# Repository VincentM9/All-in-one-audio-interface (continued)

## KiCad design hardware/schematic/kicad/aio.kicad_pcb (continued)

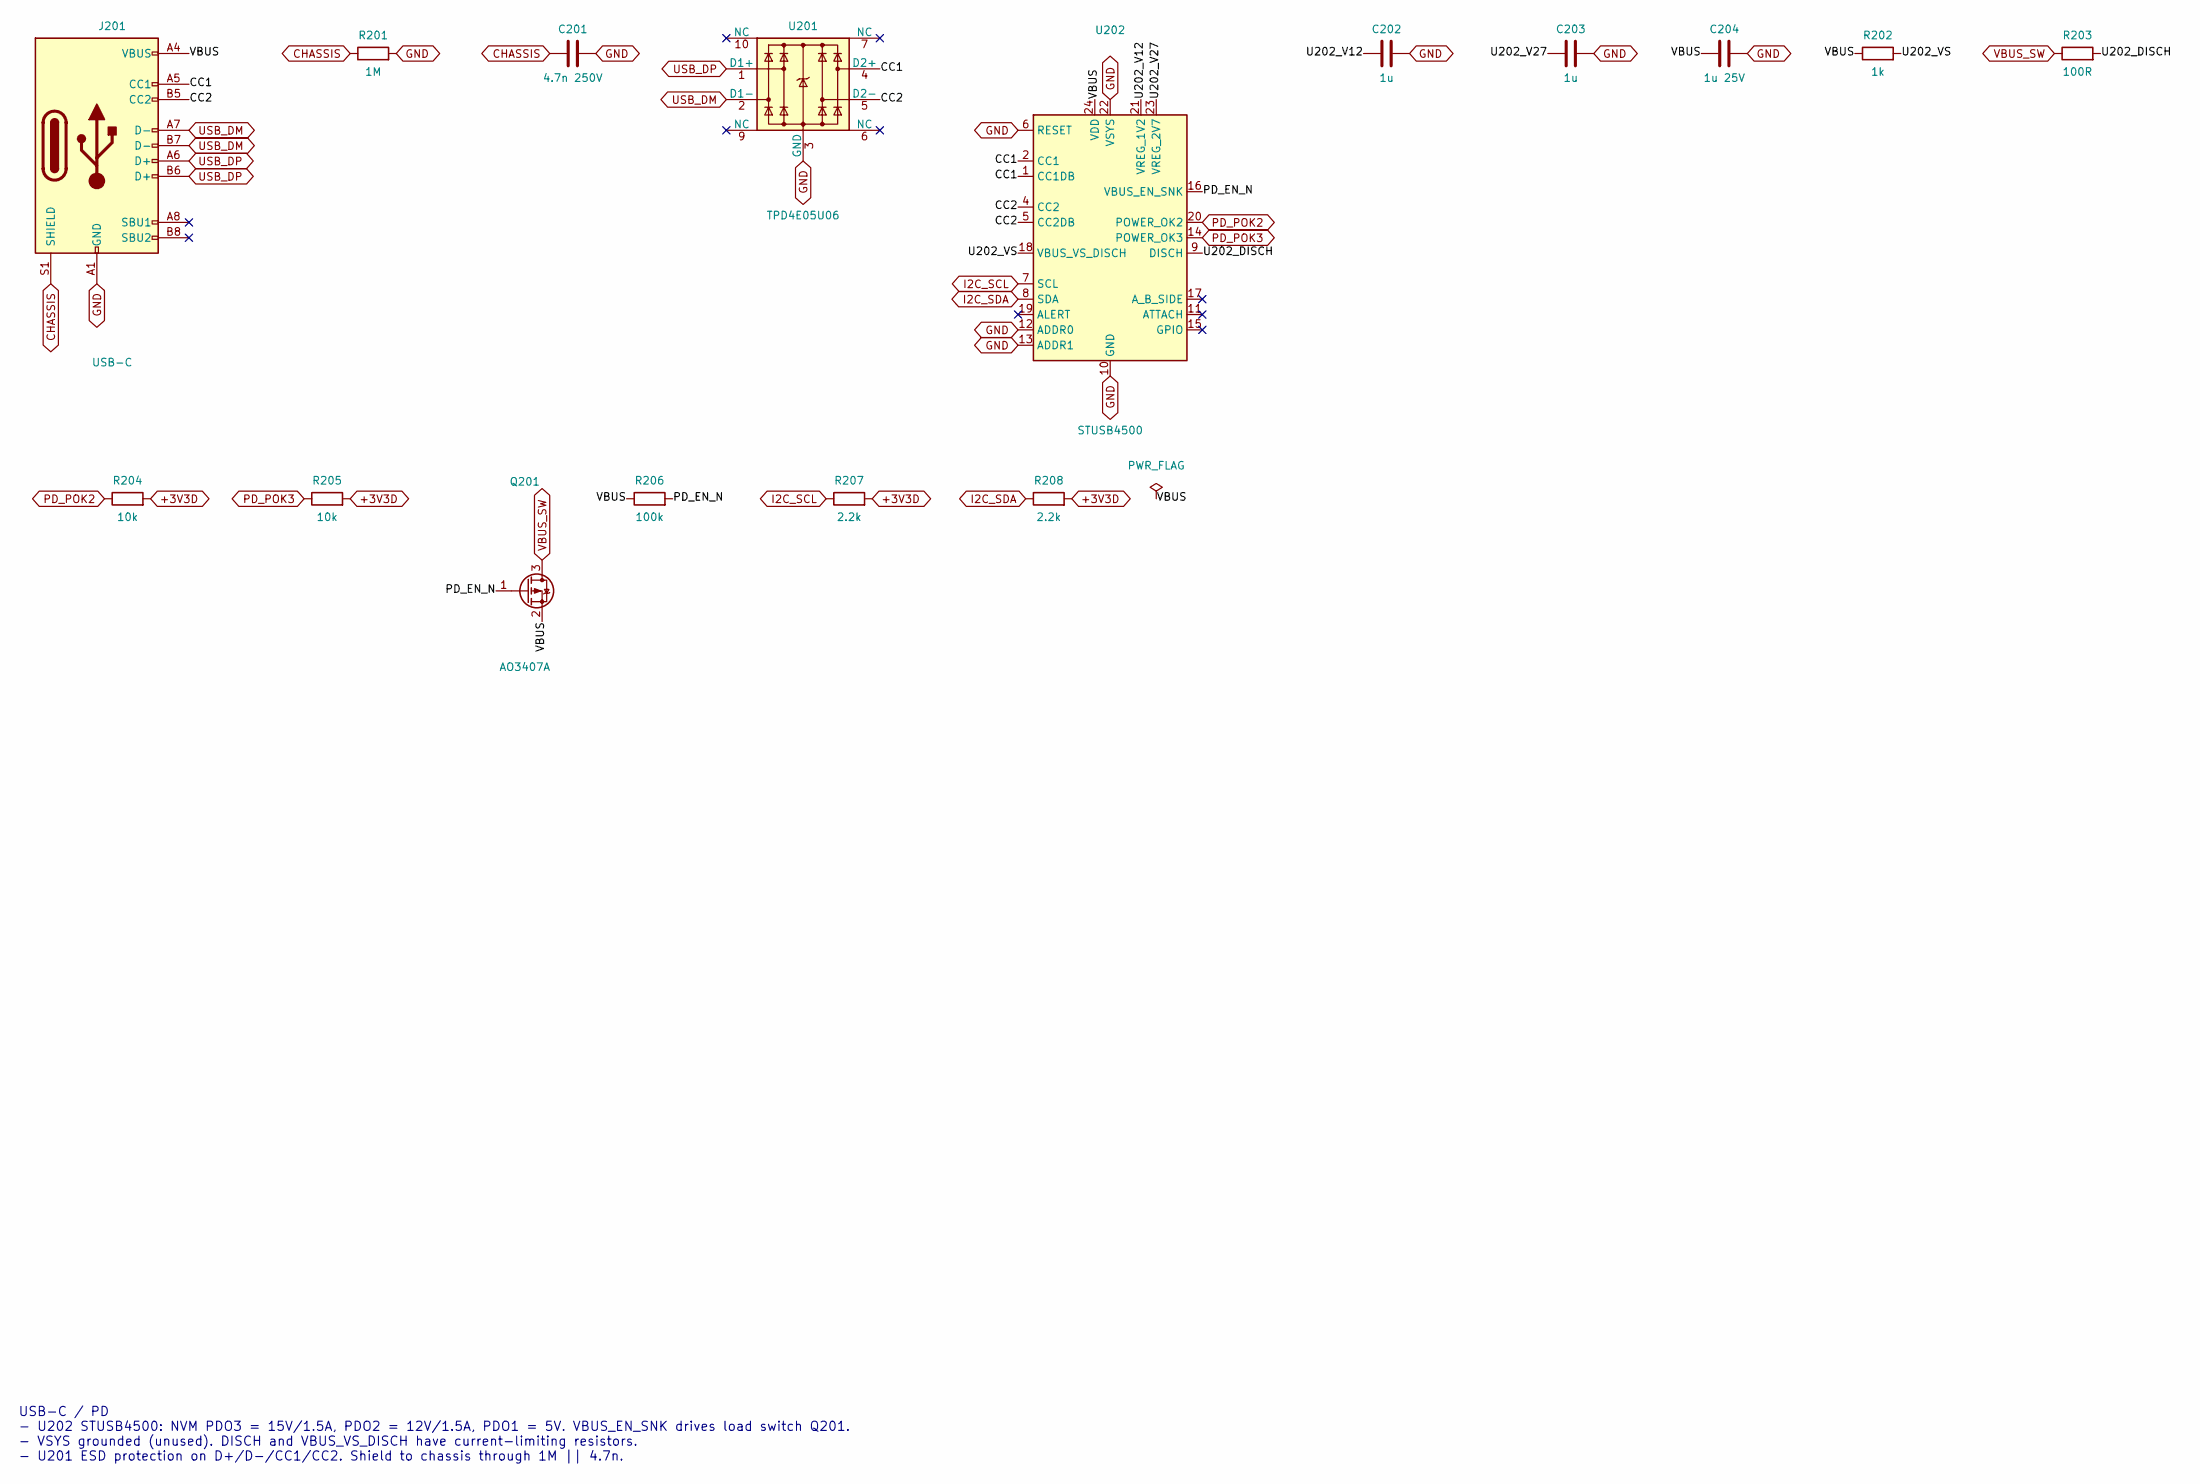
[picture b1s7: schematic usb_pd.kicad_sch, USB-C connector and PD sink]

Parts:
C201: 4.7n 250V; C_1206_3216Metric
C202, C203: 1u; C_0603_1608Metric
C204: 1u 25V; C_0805_2012Metric
J201: USB-C; USB_C_Receptacle_GCT_USB4105-xx-A_16P_TopMnt_Horizontal; MPN USB4105-GF-A
Q201: AO3407A; SOT-23; MPN AO3407A
R201: 1M; R_0603_1608Metric
R202: 1k; R_0603_1608Metric
R203: 100R; R_0805_2012Metric
R204, R205: 10k; R_0603_1608Metric
R206: 100k; R_0603_1608Metric
R207, R208: 2.2k; R_0603_1608Metric
U201: TPD4E05U06; USON-10_2.5x1.0mm_P0.5mm; MPN TPD4E05U06DQAR
U202: STUSB4500; QFN-24-1EP_4x4mm_P0.5mm_EP2.7x2.7mm; MPN STUSB4500QTR

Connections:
+3V3D: R204.2, R205.2, R207.2, R208.2; also elsewhere on the board
CC1: J201.A5 (CC1), U201.4 (D2+), U202.1 (CC1DB), U202.2 (CC1)
CC2: J201.B5 (CC2), U201.5 (D2-), U202.4 (CC2), U202.5 (CC2DB)
CHASSIS: C201.1, J201.S1 (SHIELD), R201.1; also elsewhere on the board
GND: C201.2, C202.2, C203.2, C204.2, J201.A1 (GND), J201.A12 (GND), J201.B1 (GND), J201.B12 (GND), R201.2, U201.3 (GND), U201.8 (GND), U202.6 (RESET), U202.10 (GND), U202.12 (ADDR0), U202.13 (ADDR1), U202.22 (VSYS), U202.25 (GND); also elsewhere on the board
I2C_SCL: R207.1, U202.7 (SCL)
I2C_SDA: R208.1, U202.8 (SDA)
PD_EN_N: Q201.1 (G), R206.2, U202.16 (VBUS_EN_SNK)
PD_POK2: R204.1, U202.20 (POWER_OK2)
PD_POK3: R205.1, U202.14 (POWER_OK3)
U202_DISCH: R203.2, U202.9 (DISCH)
U202_V12: C202.1, U202.21 (VREG_1V2)
U202_V27: C203.1, U202.23 (VREG_2V7)
U202_VS: R202.2, U202.18 (VBUS_VS_DISCH)
USB_DM: J201.A7 (D-), J201.B7 (D-), U201.2 (D1-)
USB_DP: J201.A6 (D+), J201.B6 (D+), U201.1 (D1+)
VBUS: C204.1, J201.A4 (VBUS), J201.A9 (VBUS), J201.B4 (VBUS), J201.B9 (VBUS), Q201.2 (S), R202.1, R206.1, U202.24 (VDD)
VBUS_SW: Q201.3 (D), R203.1; also elsewhere on the board

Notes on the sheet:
USB-C / PD - U202 STUSB4500: NVM PDO3 = 15V/1.5A, PDO2 = 12V/1.5A, PDO1 = 5V. VBUS_EN_SNK drives load switch Q201. - VSYS grounded (unused). DISCH and VBUS_VS_DISCH have current-limiting resistors. - U201 ESD protection on D+/D-/CC1/CC2. Shield to chassis through 1M || 4.7n.

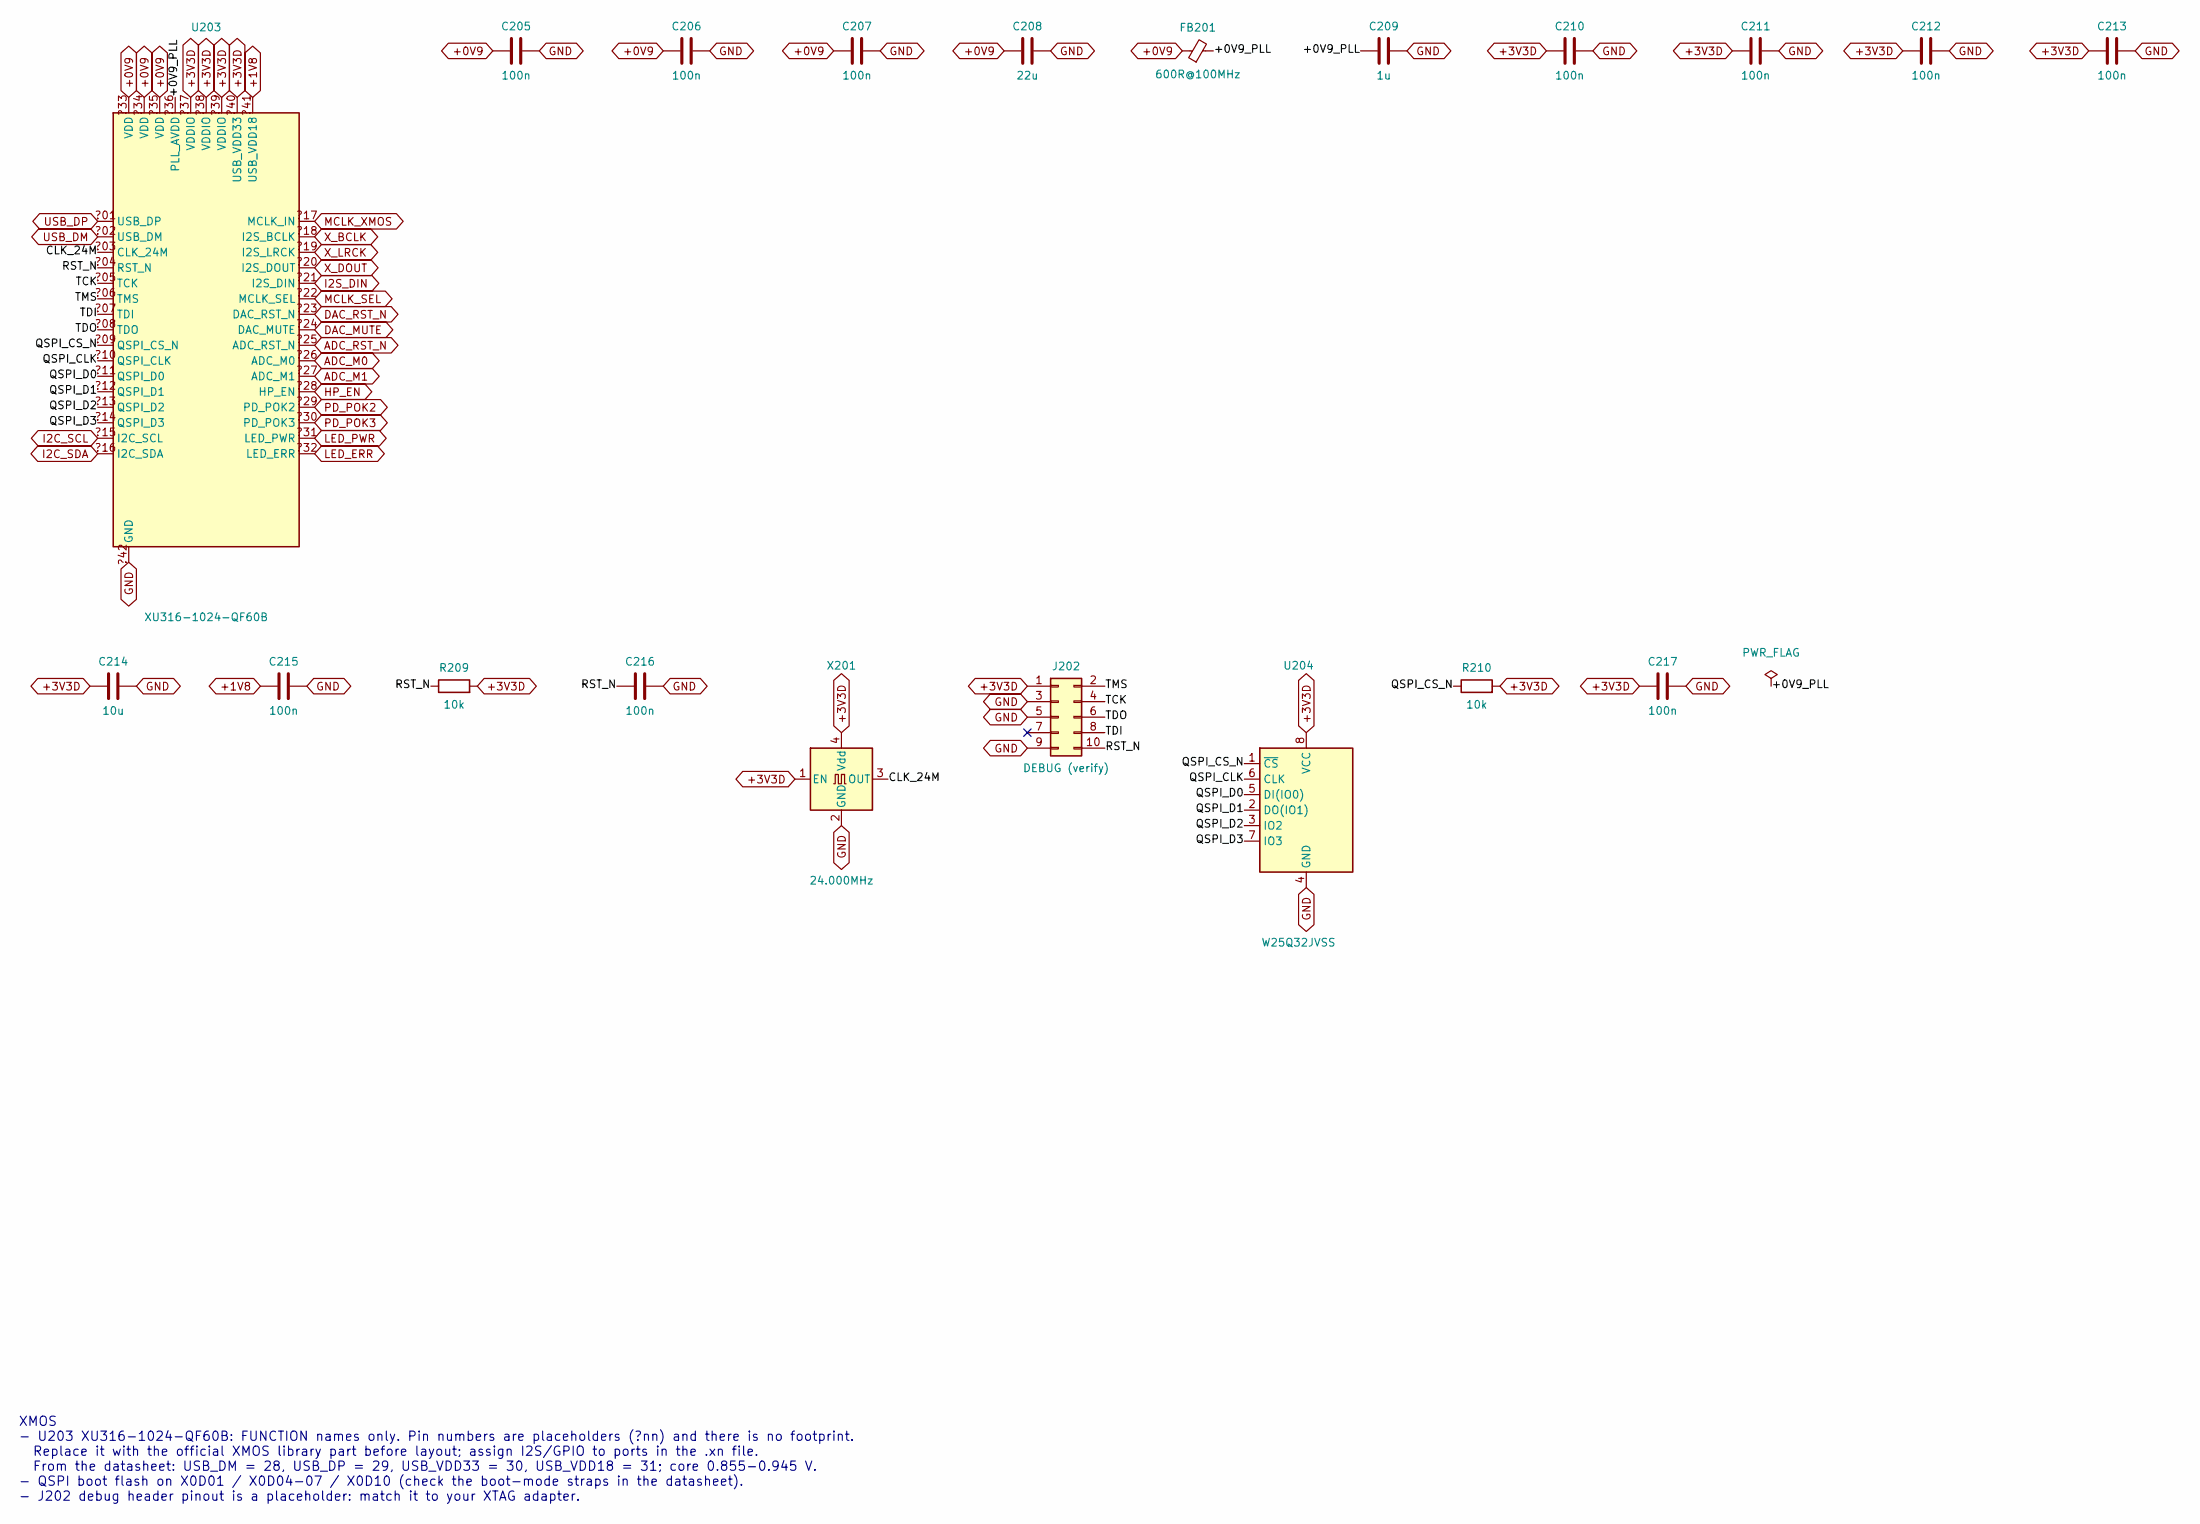
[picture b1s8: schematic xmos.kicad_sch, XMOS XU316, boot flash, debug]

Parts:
C205, C206, C207, C210, C211, C212, C213, C215, C216, C217: 100n; C_0603_1608Metric
C208: 22u; C_0805_2012Metric
C209: 1u; C_0603_1608Metric
C214: 10u; C_0805_2012Metric
FB201: 600R@100MHz; L_0805_2012Metric
J202: DEBUG (verify); PinHeader_2x05_P1.27mm_Vertical
R209, R210: 10k; R_0603_1608Metric
U203: XU316-1024-QF60B; MPN XU316-1024-QF60B-C24
U204: W25Q32JVSS; SOIC-8_5.23x5.23mm_P1.27mm; MPN W25Q32JVSSIQ
X201: 24.000MHz; Oscillator_SMD_Abracon_ASE-4Pin_3.2x2.5mm; MPN ASE-24.000MHZ-LC-T

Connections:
+0V9: C205.1, C206.1, C207.1, C208.1, FB201.1, U203.?33 (VDD), U203.?34 (VDD), U203.?35 (VDD); also elsewhere on the board
+0V9_PLL: C209.1, FB201.2, U203.?36 (PLL_AVDD)
+1V8: C215.1, U203.?41 (USB_VDD18); also elsewhere on the board
+3V3D: C210.1, C211.1, C212.1, C213.1, C214.1, C217.1, J202.1, R209.2, R210.2, U203.?37 (VDDIO), U203.?38 (VDDIO), U203.?39 (VDDIO), U203.?40 (USB_VDD33), U204.8 (VCC), X201.1 (EN), X201.4 (Vdd); also elsewhere on the board
CLK_24M: U203.?03 (CLK_24M), X201.3 (OUT)
GND: C205.2, C206.2, C207.2, C208.2, C209.2, C210.2, C211.2, C212.2, C213.2, C214.2, C215.2, C216.2, C217.2, J202.3, J202.5, J202.9, U203.?42 (GND), U204.4 (GND), X201.2 (GND); also elsewhere on the board
QSPI_CLK: U203.?10 (QSPI_CLK), U204.6 (CLK)
QSPI_CS_N: R210.1, U203.?09 (QSPI_CS_N), U204.1 (~CS)
QSPI_D0: U203.?11 (QSPI_D0), U204.5 (DI(IO0))
QSPI_D1: U203.?12 (QSPI_D1), U204.2 (DO(IO1))
QSPI_D2: U203.?13 (QSPI_D2), U204.3 (IO2)
QSPI_D3: U203.?14 (QSPI_D3), U204.7 (IO3)
RST_N: C216.1, J202.10, R209.1, U203.?04 (RST_N)
TCK: J202.4, U203.?05 (TCK)
TDI: J202.8, U203.?07 (TDI)
TDO: J202.6, U203.?08 (TDO)
TMS: J202.2, U203.?06 (TMS)

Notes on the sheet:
XMOS - U203 XU316-1024-QF60B: FUNCTION names only. Pin numbers are placeholders (?nn) and there is no footprint. Replace it with the official XMOS library part before layout; assign I2S/GPIO to ports in the .xn file. From the datasheet: USB_DM = 28, USB_DP = 29, USB_VDD33 = 30, USB_VDD18 = 31; core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

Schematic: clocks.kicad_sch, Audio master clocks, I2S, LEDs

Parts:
C218, C219, C220: 100n; C_0603_1608Metric
D201: green; LED_0805_2012Metric
D202: red; LED_0805_2012Metric
R211, R212, R213: 22R; R_0603_1608Metric
R214, R215, R216: 33R; R_0603_1608Metric
R217, R218: 330R; R_0603_1608Metric
U205: 74LVC1G3157; SOT-363_SC-70-6; MPN SN74LVC1G3157DCKR
X202: 24.576MHz; Oscillator_SMD_Abracon_ASE-4Pin_3.2x2.5mm; MPN NZ2520SDA-24.576M (low phase noise)
X203: 22.5792MHz; Oscillator_SMD_Abracon_ASE-4Pin_3.2x2.5mm; MPN NZ2520SDA-22.5792M (low phase noise)

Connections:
+3V3A: C218.1, C219.1, C220.1, U205.5 (VCC), X202.1 (EN), X202.4 (Vdd), X203.1 (EN), X203.4 (Vdd); also elsewhere on the board
GND: C218.2, C219.2, C220.2, D201.1 (K), D202.1 (K), U205.2 (GND), X202.2 (GND), X203.2 (GND); also elsewhere on the board
I2S_BCLK: R214.2; also elsewhere on the board
I2S_DOUT: R216.2; also elsewhere on the board
I2S_LRCK: R215.2; also elsewhere on the board
LED_ERR: R218.1
LED_ERR_A: D202.2 (A), R218.2
LED_PWR: R217.1
LED_PWR_A: D201.2 (A), R217.2
MCLK_44: U205.1, X203.3 (OUT)
MCLK_48: U205.3, X202.3 (OUT)
MCLK_ADC: R213.2; also elsewhere on the board
MCLK_DAC: R212.2; also elsewhere on the board
MCLK_MUX: R211.1, R212.1, R213.1, U205.4
MCLK_SEL: U205.6
MCLK_XMOS: R211.2
X_BCLK: R214.1
X_DOUT: R216.1
X_LRCK: R215.1

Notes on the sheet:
CLOCKS / I2S - X202 24.576 MHz (48 kHz family) and X203 22.5792 MHz (44.1 kHz family), selected by U205 (MCLK_SEL = 0 -> 48k). - Mux output fans out through 22R to XMOS, DAC and ADC. XMOS drives BCLK / LRCK / DOUT through 33R.

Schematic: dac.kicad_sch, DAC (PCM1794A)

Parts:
C301, C303, C305, C307, C309, C310: 10u; C_0805_2012Metric
C302, C304, C306, C308: 100n; C_0603_1608Metric
R301: 16k; R_0603_1608Metric
R302, R303, R304, R306: 10k; R_0603_1608Metric
R305, R307: 10k; R_0603_1608Metric; not fitted
U301: PCM1794A; SSOP-28_5.3x10.2mm_P0.65mm; MPN PCM1794ADBR

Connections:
+3V3A: C307.1, C308.1, R303.2, R305.2, R307.2, U301.9 (VDD); also elsewhere on the board
+5VA: C301.1, C302.1, C303.1, C304.1, C305.1, C306.1, U301.15 (VCC2R), U301.23 (VCC1), U301.28 (VCC2L); also elsewhere on the board
DAC_FMT0: R304.1, R305.1, U301.11 (FMT0)
DAC_FMT1: R306.1, R307.1, U301.12 (FMT1)
DAC_MUTE: R303.1, U301.10 (MUTE)
DAC_RST_N: R302.1, U301.14 (~RST)
GND: C301.2, C302.2, C303.2, C304.2, C305.2, C306.2, C307.2, C308.2, C309.2, C310.2, R301.2, R302.2, R304.2, R306.2, U301.1 (MONO), U301.2 (CHSL), U301.3 (DEM), U301.8 (DGND), U301.16 (AGND3R), U301.19 (AGND1), U301.24 (AGND2), U301.27 (AGND3L); also elsewhere on the board
I2S_BCLK: U301.6 (BCK); also elsewhere on the board
I2S_DOUT: U301.5 (DATA); also elsewhere on the board
I2S_LRCK: U301.4 (LRCK); also elsewhere on the board
IL_N: U301.26 (IOUTL-); also elsewhere on the board
IL_P: U301.25 (IOUTL+); also elsewhere on the board
IREF: R301.1, U301.20 (IREF)
IR_N: U301.18 (IOUTR-); also elsewhere on the board
IR_P: U301.17 (IOUTR+); also elsewhere on the board
MCLK_DAC: U301.7 (SCK); also elsewhere on the board
VCOML: C309.1, U301.22 (VCOML)
VCOMR: C310.1, U301.21 (VCOMR)

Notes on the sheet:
DAC NOTES - U301 PCM1794A (hardware control). Output 7.8 mA p-p per pin around ~-6.2 mA. - I/V 750R: 5.85 V p-p per leg around +4.65 V. Diff stage gain 0.5 -> ~2.07 Vrms single-ended. Diff stage inputs are swapped (P from IOUT-, N from IOUT+) so the output is non-inverted. - FMT0/FMT1 straps: fit p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

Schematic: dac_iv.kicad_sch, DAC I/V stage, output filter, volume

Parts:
C311, C312, C315, C316: 2.2n C0G; C_0603_1608Metric
C313, C314, C317, C318, C319, C320: 100n; C_0603_1608Metric
C321, C322, C324, C325: 1.5n C0G; C_0603_1608Metric
C323, C326: 4.7u film; C_Rect_L18.0mm_W8.0mm_P15.00mm_FKS3_FKP3; MPN WIMA MKS4 4.7uF 63V
R308, R309, R310, R311: 750R 0.1%; R_0603_1608Metric
R312, R314, R316, R318: 2.00k 0.1%; R_0603_1608Metric
R313, R315, R317, R319: 1.00k 0.1%; R_0603_1608Metric
RV301: 10k log dual; Potentiometer_Alps_RK097_Dual_Horizontal; MPN ALPS RK097 dual 10k log (A)
U302, U303, U304: OPA1612; SOIC-8_3.9x4.9mm_P1.27mm; MPN OPA1612AIDR

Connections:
+16V: C313.1, C317.1, C319.1, U302.8 (V+), U303.8 (V+), U304.8 (V+); also elsewhere on the board
-16V: C314.1, C318.1, C320.1, U302.4 (V-), U303.4 (V-), U304.4 (V-); also elsewhere on the board
DAC_L_OUT: C322.2, C323.1, R315.2, U304.1
DAC_R_OUT: C325.2, C326.1, R319.2, U304.7
DL_N: C322.1, R314.2, R315.1, U304.2 (-)
DL_P: C321.1, R312.2, R313.1, U304.3 (+)
DR_N: C325.1, R318.2, R319.1, U304.6 (-)
DR_P: C324.1, R316.2, R317.1, U304.5 (+)
GND: C313.2, C314.2, C317.2, C318.2, C319.2, C320.2, C321.2, C324.2, R313.2, R317.2, RV301.3, RV301.6, U302.3 (+), U302.5 (+), U303.3 (+), U303.5 (+); also elsewhere on the board
HP_IN_L: RV301.2; also elsewhere on the board
HP_IN_R: RV301.5; also elsewhere on the board
IL_N: C312.2, R309.2, U302.6 (-); also elsewhere on the board
IL_P: C311.2, R308.2, U302.2 (-); also elsewhere on the board
IR_N: C316.2, R311.2, U303.6 (-); also elsewhere on the board
IR_P: C315.2, R310.2, U303.2 (-); also elsewhere on the board
POT_L: C323.2, RV301.1
POT_R: C326.2, RV301.4
VL_N: C312.1, R309.1, R312.1, U302.7
VL_P: C311.1, R308.1, R314.1, U302.1
VR_N: C316.1, R311.1, R316.1, U303.7
VR_P: C315.1, R310.1, R318.1, U303.1

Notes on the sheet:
I/V AND OUTPUT - I/V 750R || 2.2n per leg: 5.85 V p-p around +4.65 V. Diff stage gain 0.5 -> ~2.07 Vrms single-ended. - Diff stage inputs are crossed (P from IOUT-, N from IOUT+) so the output is not inverted. - 4.7 uF film caps block DC into the volume pot. Use 0.1 % resistors in the diff stage.

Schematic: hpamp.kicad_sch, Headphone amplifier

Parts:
C401, C402, C409, C416: 100n; C_0603_1608Metric
C403, C410: 470p C0G; C_0603_1608Metric
C404, C411: 22p C0G; C_0603_1608Metric
C405, C406, C407, C408, C412, C413, C414, C415: 10u 25V; C_1210_3225Metric
C417, C418: 220u 25V; CP_Elec_10x10
R401, R411: 100R; R_0603_1608Metric
R402, R412: 100k; R_0603_1608Metric
R403, R413: 2.00k 0.1%; R_0603_1608Metric
R404, R414: 4.02k 0.1%; R_0603_1608Metric
R405, R415: 576R 0.1%; R_0603_1608Metric
R406, R408, R416, R418: 47R; R_0603_1608Metric
R407, R409, R417, R419: 2.2R 1W; R_2512_6332Metric
R410, R420: 10R; R_0805_2012Metric
SW401: GAIN H/L; SW_DPDT_CK_JS202011JCQN; MPN JS202011JCQN
U401: OPA1612; SOIC-8_3.9x4.9mm_P1.27mm; MPN OPA1612AIDR
U402, U403, U404, U405: LME49600; TO-263-5_TabPin3; MPN LME49600TS/NOPB

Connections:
+16V: C401.1, C405.1, C407.1, C412.1, C414.1, C417.1, U401.8 (V+), U402.5 (V+), U403.5 (V+), U404.5 (V+), U405.5 (V+); also elsewhere on the board
-16V: C402.1, C406.2, C408.2, C413.2, C415.2, C418.2, U401.4 (V-), U402.3 (V-), U403.3 (V-), U404.3 (V-), U405.3 (V-); also elsewhere on the board
AMP_INL: C403.1, R401.2, R402.1, U401.3 (+)
AMP_INR: C410.1, R411.2, R412.1, U401.5 (+)
BIN_L1: R406.2, U402.2 (IN)
BIN_L2: R408.2, U403.2 (IN)
BIN_R1: R416.2, U404.2 (IN)
BIN_R2: R418.2, U405.2 (IN)
BO_L1: R407.1, U402.4
BO_L2: R409.1, U403.4
BO_R1: R417.1, U404.4
BO_R2: R419.1, U405.4
FB_L: C404.2, R403.2, R404.1, R405.1, U401.2 (-)
FB_R: C411.2, R413.2, R414.1, R415.1, U401.6 (-)
GAIN_L: R405.2, SW401.2 (B)
GAIN_R: R415.2, SW401.5 (B)
GND: C401.2, C402.2, C403.2, C405.2, C406.1, C407.2, C408.1, C409.2, C410.2, C412.2, C413.1, C414.2, C415.1, C416.2, C417.2, C418.1, R402.2, R404.2, R412.2, R414.2, SW401.1 (A), SW401.4 (A); also elsewhere on the board
HP_IN_L: R401.1; also elsewhere on the board
HP_IN_R: R411.1; also elsewhere on the board
OA_L: R406.1, R408.1, U401.1
OA_R: R416.1, R418.1, U401.7
OUT_L: C404.1, R403.1, R407.2, R409.2, R410.1; also elsewhere on the board
OUT_R: C411.1, R413.1, R417.2, R419.2, R420.1; also elsewhere on the board
ZB_L: C409.1, R410.2
ZB_R: C416.1, R420.2

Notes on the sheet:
HEADPHONE AMP NOTES - Per channel: OPA1612 + 2x LME49600 inside the loop, 2.2R ballast each, feedback from OUT_x. - Gain: 1 + 2.00k / (4.02k || 576R) = 4.97 (SW401 closed, High) or 1.50 (open, Low). - 2 W into 32R = 8 Vrms, 354 mA peak (177 mA per LME49600, rated 250 mA). - Relay K401 (NO contacts)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

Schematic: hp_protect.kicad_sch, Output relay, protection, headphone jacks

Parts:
C419: 10u; C_0805_2012Metric
C420, C421: 100n; C_0603_1608Metric
C422, C423: 47u 25V; CP_Elec_8x10
D401: 1N4148W; D_SOD-123
D402: BAT54; D_SOD-123; MPN BAT54W
J401: 6.35mm; Jack_6.35mm_Neutrik_NMJ6HCD2_Horizontal; MPN NMJ6HCD2
J402: 3.5mm; Jack_3.5mm_CUI_SJ1-3533NG_Horizontal; MPN SJ1-3533NG
K401: G6K-2F-Y 3VDC; Relay_DPDT_Omron_G6K-2F-Y; MPN G6K-2F-Y DC3
Q401: 2N7002; SOT-23; MPN 2N7002
Q402, Q403: BC847; SOT-23; MPN BC847B
R421: 1k; R_0603_1608Metric
R422: 220k; R_0603_1608Metric
R423, R425: 100k; R_0603_1608Metric
R424: 10.7k; R_0603_1608Metric
R426: 16.9k; R_0603_1608Metric
R427, R428, R431, R432: 10k; R_0603_1608Metric
R429, R430: 47k; R_0603_1608Metric
U406: LM393; SOIC-8_3.9x4.9mm_P1.27mm; MPN LM393DR

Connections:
+3V3D: C420.1, D401.1 (K), K401.1, R422.1, R426.1, R427.1, U406.8 (V+); also elsewhere on the board
+18V4: R423.1; also elsewhere on the board
-16V: R425.1; also elsewhere on the board
DCB: Q402.1 (B), R431.2
DCE: Q403.2 (E), R432.2
DCMID: C422.2, C423.2
DCSUM: C422.1, R429.2, R430.2, R431.1, R432.1
GND: C419.2, C420.2, C421.2, C423.1, J401.S, J402.S, Q401.2 (S), Q402.2 (E), Q403.1 (B), R424.2, R428.2, U406.4 (V-); also elsewhere on the board
HPJ_L: J401.T, J402.T, K401.4
HPJ_R: J401.R, J402.R, K401.5
HP_EN: D402.1 (K)
MON_N16: R425.2, R426.2, U406.6 (-)
MON_P18: R423.2, R424.1, U406.3 (+)
OUT_L: K401.3, R429.1; also elsewhere on the board
OUT_R: K401.6, R430.1; also elsewhere on the board
RDRV: C419.1, D402.2 (A), Q402.3 (C), Q403.3 (C), R421.1, R422.2, U406.1, U406.7
RLY_DRV: D401.2 (A), K401.8, Q401.3 (D)
RLY_G: Q401.1 (G), R421.2
VREF_1V65: C421.1, R427.2, R428.1, U406.2 (-), U406.5 (+)

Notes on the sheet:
PROTECTION - Relay K401 (NO contacts) connects the jacks only when RDRV is high: ~2-3 s after power-up (220k / 10u), released at once if +18V4 sags (U406A), -16V collapses (U406B), either output has DC beyond about +-0.6 V (Q402 / Q403), or the XMOS pulls HP_EN low (BAT54 D402).

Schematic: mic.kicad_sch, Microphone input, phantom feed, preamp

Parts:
C501, C502: 100p C0G; C_0603_1608Metric
C503: 470p C0G; C_0603_1608Metric
C504, C505, C506: 47u 63V; CP_Elec_10x10
C507, C508: 220u 25V; CP_Elec_10x10
C509, C510: 100n; C_0603_1608Metric
C511: 4700u 6.3V; CP_Elec_10x10
D501: red 48V; LED_0805_2012Metric
D502, D503, D504, D505: 1N4004; D_DO-41_SOD81_P10.16mm_Horizontal; MPN 1N4004
D506, D507: SMBJ18CA; D_SMB; MPN SMBJ18CA
FB501, FB502: 600R@100MHz; L_0805_2012Metric
J501: NCJ6FI-H; Jack_XLR-6.35mm_Neutrik_NCJ6FI-H_Horizontal; MPN NCJ6FI-H
R501: 47R; R_0603_1608Metric
R502: 22k; R_0603_1608Metric
R503, R504: 6.81k 0.1%; R_0805_2012Metric
R505, R506: 2.21k; R_0603_1608Metric
R507, R508, R509, R510: 10R; R_0805_2012Metric
R511: 5.1R; R_0603_1608Metric
RV501: 10k rev-log (C); Potentiometer_Alps_RK097_Single_Horizontal; MPN 10k C-taper
SW501: +48V; SW_Slide_SPDT_Straight_CK_OS102011MS2Q; MPN SPST latching (panel)
U501: THAT1512S08; SOIC-8_3.9x4.9mm_P1.27mm; MPN THAT1512S08-U

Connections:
+16V: D502.1 (K), D504.1 (K), D506.1 (A1), R509.1; also elsewhere on the board
+16V_MIC: C507.1, C509.1, R509.2, U501.7 (V+); also elsewhere on the board
+48V: SW501.1 (A); also elsewhere on the board
-16V: D503.2 (A), D505.2 (A), D507.2 (A2), R510.1; also elsewhere on the board
-16V_MIC: C508.2, C510.1, R510.2, U501.4 (V-); also elsewhere on the board
CHASSIS: J501.G; also elsewhere on the board
GND: C501.2, C502.2, C504.2, C507.2, C508.1, C509.2, C510.2, D501.1 (K), D506.2 (A2), D507.1 (A1), J501.1, R505.2, R506.2, U501.5 (Ref); also elsewhere on the board
MIC_N: C502.1, C503.2, C506.1, FB502.2, R504.2
MIC_P: C501.1, C503.1, C505.1, FB501.2, R503.2
P48: C504.1, R501.2, R502.1, R503.1, R504.1
P48_LED: D501.2 (A), R502.2
P48_SW: R501.1, SW501.2 (B)
PRE_N: C506.2, R506.1, R508.1
PRE_OUT: U501.6 (Out); also elsewhere on the board
PRE_P: C505.2, R505.1, R507.1
RG_A: R511.1, U501.1 (Rg1)
RG_B: C511.2, U501.8 (Rg2)
RG_C: R511.2, RV501.1
RG_D: C511.1, RV501.2, RV501.3
THAT_N: D504.2 (A), D505.1 (K), R508.2, U501.2 (-In)
THAT_P: D502.2 (A), D503.1 (K), R507.2, U501.3 (+In)
XLR_COLD: FB502.1, J501.3
XLR_HOT: FB501.1, J501.2

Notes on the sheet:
MIC INPUT NOTES - P48 phantom per IEC 61938: 6.81k 0.1 % matched feed pair, open-circuit ~48.6 V. SW501 switches it. - Hot-plug protection: 10R series + 1N4004 clamps to the +-16V rails + SMBJ18CA TVS on the rails. - U501 THAT1512: G = 0.5 + 5k / (5.1R + RV501) -> 0 dB to ~60 dB. 4700u cap blocks D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

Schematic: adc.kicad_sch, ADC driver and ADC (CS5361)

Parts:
C512, C513, C519, C521, C523, C524, C525: 100n; C_0603_1608Metric
C514: 47p C0G; C_0603_1608Metric
C515, C516: 22u 25V NP; CP_Elec_8x10
C517: 2.7n C0G; C_0603_1608Metric
C518: 47u; C_1206_3216Metric
C520, C522: 10u; C_0805_2012Metric
D508, D509: BAT54S; SOT-23; MPN BAT54S
D510: red CLIP; LED_0805_2012Metric
R512, R513: 2.00k 0.1%; R_0603_1608Metric
R514, R515: 100k; R_0603_1608Metric
R516, R517: 49.9R; R_0603_1608Metric
R518, R519, R520: 10k; R_0603_1608Metric
R521: 1k; R_0603_1608Metric
U502: OPA1612; SOIC-8_3.9x4.9mm_P1.27mm; MPN OPA1612AIDR
U503: CS5361; TSSOP-24_4.4x7.8mm_P0.65mm; MPN CS5361-KZZ

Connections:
+3V3A: C524.1, C525.1, R521.1, U503.6 (VD), U503.8 (VL), U503.12 (I2S/~LJ); also elsewhere on the board
+5VA: C522.1, C523.1, D508.2 (K), D509.2 (K), U503.19 (VA); also elsewhere on the board
+16V_MIC: C512.1, U502.8 (V+); also elsewhere on the board
-16V_MIC: C513.1, U502.4 (V-); also elsewhere on the board
ADC_M0: R519.1, U503.13 (M0)
ADC_M1: R520.1, U503.14 (M1)
ADC_OVFL: D510.1 (K), U503.15 (~OVFL)
ADC_RST_N: R518.1, U503.1 (~RST)
AINL_N: C517.2, D509.3 (COM), R517.2, U503.17 (AINL-)
AINL_P: C517.1, D508.3 (COM), R516.2, U503.16 (AINL+)
AINN_B: C516.2, R515.1, R517.1
AINP_B: C515.2, R514.1, R516.1
CLIP_A: D510.2 (A), R521.2
DRV_N: C514.2, C516.1, R513.2, U502.7
DRV_P: C515.1, U502.1, U502.2 (-)
FILT: C518.1, C519.1, U503.24 (FILT+)
GND: C512.2, C513.2, C518.2, C519.2, C520.2, C521.2, C522.2, C523.2, C524.2, C525.2, D508.1 (A), D509.1 (A), R518.2, R519.2, R520.2, U502.5 (+), U503.2 (M/~S), U503.7 (GND), U503.10 (MDIV), U503.11 (~HPF), U503.18 (GND), U503.23 (REFGND); also elsewhere on the board
I2S_BCLK: U503.4 (SCLK); also elsewhere on the board
I2S_DIN: U503.9 (SDOUT)
I2S_LRCK: U503.3 (LRCK); also elsewhere on the board
INV_N: C514.1, R512.2, R513.1, U502.6 (-)
MCLK_ADC: U503.5 (MCLK); also elsewhere on the board
PRE_OUT: R512.1, U502.3 (+); also elsewhere on the board
VQ: C520.1, C521.1, R514.2, R515.2, U503.20 (AINR-), U503.21 (AINR+), U503.22 (VQ)

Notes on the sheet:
ADC - U502 makes a differential signal: 1 Vrms at PRE_OUT = 2 Vrms differential = 0 dBFS on the CS5361 (full scale = 1.13 x VA = 5.65 V p-p differential at VA = 5 V). - U503 CS5361: slave mode, I2S, HPF on. M0/M1 speed mode set by XMOS per sample rate. Unused right channel tied to VQ. OVFL drives t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

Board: 2 copper layers, 356 parts (0 on the bottom side), 180 nets, no tracks yet.

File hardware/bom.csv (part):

Qty,References,Value,MPN,Footprint,Symbol,DNP
5,C101 C417 C418 C507 C508,220u 25V,,Capacitor_SMD:CP_Elec_10x10,Device:C_Polarized,
19,C102 C107 C118 C129 C136 C137 C141 C142 C145 C151 C155 C405 C406 C407 C408 C412 C413 C414 C415,10u 25V,,Capacitor_SMD:C_1210_3225Metric,Device:C,
3,C103 C114 C125,4.7u 16V,,Capacitor_SMD:C_0805_2012Metric,Device:C,
41,C104 C115 C126 C205 C206 C207 C210 C211 C212 C213 C215 C216 C217 C218 C219 C220 C302 C304 C306 C308 C313 C314 C317 C318 C319 C320 C401 C402 C409 C416 C420 C421 C509 C510 C512 C513 C519 C521 C523 C524 C525,100n,,Capacitor_SMD:C_0603_1608Metric,Device:C,
3,C105 C116 C127,6.8n,,Capacitor_SMD:C_0603_1608Metric,Device:C,
3,C106 C117 C128,100p,,Capacitor_SMD:C_0603_1608Metric,Device:C,
2,C108 C119,4.7u 50V,,Capacitor_SMD:C_1210_3225Metric,Device:C,
6,C109 C110 C112 C120 C121 C123,22u 50V,,Capacitor_SMD:C_1210_3225Metric,Device:C,
4,C111 C113 C122 C124,100u 35V,,Capacitor_SMD:CP_Elec_8x10,Device:C_Polarized,
3,C130 C131 C132,2.2u 100V,,Capacitor_SMD:C_1210_3225Metric,Device:C,
1,C133,100u 63V,,Capacitor_SMD:CP_Elec_10x10,Device:C_Polarized,
4,C134 C504 C505 C506,47u 63V,,Capacitor_SMD:CP_Elec_10x10,Device:C_Polarized,
7,C135 C144 C158 C159 C202 C203 C209,1u,,Capacitor_SMD:C_0603_1608Metric,Device:C,
2,C138 C143,100u 25V,,Capacitor_SMD:CP_Elec_8x10,Device:C_Polarized,
2,C139 C140,10n,,Capacitor_SMD:C_0603_1608Metric,Device:C,
1,C146,10u 16V,,Capacitor_SMD:C_1206_3216Metric,Device:C,
2,C147 C148,4.7u,,Capacitor_SMD:C_0805_2012Metric,Device:C,
11,C149 C214 C301 C303 C305 C307 C309 C310 C419 C520 C522,10u,,Capacitor_SMD:C_0805_2012Metric,Device:C,
2,C150 C154,3.3n,,Capacitor_SMD:C_0603_1608Metric,Device:C,
5,C152 C153 C156 C157 C208,22u,,Capacitor_SMD:C_0805_2012Metric,Device:C,
1,C201,4.7n 250V,,Capacitor_SMD:C_1206_3216Metric,Device:C,
1,C204,1u 25V,,Capacitor_SMD:C_0805_2012Metric,Device:C,
4,C311 C312 C315 C316,2.2n C0G,,Capacitor_SMD:C_0603_1608Metric,Device:C,
4,C321 C322 C324 C325,1.5n C0G,,Capacitor_SMD:C_0603_1608Metric,Device:C,
2,C323 C326,4.7u film,WIMA MKS4 4.7uF 63V,Capacitor_THT:C_Rect_L18.0mm_W8.0mm_P15.00mm_FKS3_FKP3,Device:C,
3,C403 C410 C503,470p C0G,,Capacitor_SMD:C_0603_1608Metric,Device:C,
2,C404 C411,22p C0G,,Capacitor_SMD:C_0603_1608Metric,Device:C,
2,C422 C423,47u 25V,,Capacitor_SMD:CP_Elec_8x10,Device:C_Polarized,
2,C501 C502,100p C0G,,Capacitor_SMD:C_0603_1608Metric,Device:C,
1,C511,4700u 6.3V,,Capacitor_SMD:CP_Elec_10x10,Device:C_Polarized,
1,C514,47p C0G,,Capacitor_SMD:C_0603_1608Metric,Device:C,
2,C515 C516,22u 25V NP,,Capacitor_SMD:CP_Elec_8x10,Device:C_Polarized,
1,C517,2.7n C0G,,Capacitor_SMD:C_0603_1608Metric,Device:C,
1,C518,47u,,Capacitor_SMD:C_1206_3216Metric,Device:C,
2,D101 D102,SS54,SS54,Diode_SMD:D_SMB,Device:D_Schottky,
1,D103,SMBJ16CA,SMBJ16CA,Diode_SMD:D_SMB,Device:D_TVS,
2,D104 D105,SS36,SS36,Diode_SMD:D_SMB,Device:D_Schottky,
1,D106,STPS1H100A,STPS1H100A,Diode_SMD:D_SMA,Device:D_Schottky,
1,D201,green,,LED_SMD:LED_0805_2012Metric,Device:LED,
1,D202,red,,LED_SMD:LED_0805_2012Metric,Device:LED,
1,D401,1N4148W,,Diode_SMD:D_SOD-123,Diode:1N4148W,
1,D402,BAT54,BAT54W,Diode_SMD:D_SOD-123,Device:D_Schottky,
1,D501,red 48V,,LED_SMD:LED_0805_2012Metric,Device:LED,
4,D502 D503 D504 D505,1N4004,1N4004,Diode_THT:D_DO-41_SOD81_P10.16mm_Horizontal,Diode:1N4004,
2,D506 D507,SMBJ18CA,SMBJ18CA,Diode_SMD:D_SMB,Device:D_TVS,
2,D508 D509,BAT54S,BAT54S,Package_TO_SOT_SMD:SOT-23,Diode:BAT54S,
1,D510,red CLIP,,LED_SMD:LED_0805_2012Metric,Device:LED,
3,FB201 FB501 FB502,600R@100MHz,,Inductor_SMD:L_0805_2012Metric,Device:FerriteBead_Small,
1,J101,12-15V DC,PJ-102AH,Connector_BarrelJack:BarrelJack_Horizontal,Connector:Barrel_Jack,
1,J201,USB-C,USB4105-GF-A,Connector_USB:USB_C_Receptacle_GCT_USB4105-xx-A_16P_TopMnt_Horizontal,Connector:USB_C_Receptacle_USB2.0_16P,
1,J202,DEBUG (verify),,Connector_PinHeader_1.27mm:PinHeader_2x05_P1.27mm_Vertical,Connector_Generic:Conn_02x05_Odd_Even,
1,J401,6.35mm,NMJ6HCD2,Connector_Audio:Jack_6.35mm_Neutrik_NMJ6HCD2_Horizontal,Connector_Audio:AudioJack3,
1,J402,3.5mm,SJ1-3533NG,Connector_Audio:Jack_3.5mm_CUI_SJ1-3533NG_Horizontal,Connector_Audio:AudioJack3,
1,J501,NCJ6FI-H,NCJ6FI-H,Connector_Audio:Jack_XLR-6.35mm_Neutrik_NCJ6FI-H_Horizontal,Connector_Audio:XLR3_AudioJack3_Combo_Ground,
1,K401,G6K-2F-Y 3VDC,G6K-2F-Y DC3,Relay_SMD:Relay_DPDT_Omron_G6K-2F-Y,Relay:G6K-2,
4,L101 L102 L104 L105,22u 4A,SRR1260-220M,Inductor_SMD:L_Bourns_SRR1260,Device:L,
2,L103 L106,1u,,Inductor_SMD:L_1210_3225Metric,Device:L,
1,L107,22u,,Inductor_SMD:L_Bourns_SRR1260,Device:L,
1,L108,10u,,Inductor_SMD:L_1210_3225Metric,Device:L,
2,L109 L110,2.2u,SRP5030T-2R2M,Inductor_SMD:L_Bourns_SRP5030T,Device:L,
2,Q101 Q102,IPD25N06S4L-30,IPD25N06S4L-30,Package_TO_SOT_SMD:TO-252-2,Device:Q_NMOS_GDS,
1,Q103,IPD33CN10N,IPD33CN10N G,Package_TO_SOT_SMD:TO-252-2,Device:Q_NMOS_GDS,
1,Q104,MMBTA06,MMBTA06,Package_TO_SOT_SMD:SOT-23,Device:Q_NPN_BEC,
1,Q201,AO3407A,AO3407A,Package_TO_SOT_SMD:SOT-23,Device:Q_PMOS_GSD,
1,Q401,2N7002,2N7002,Package_TO_SOT_SMD:SOT-23,Transistor_FET:2N7002,
2,Q402 Q403,BC847,BC847B,Package_TO_SOT_SMD:SOT-23,Transistor_BJT:BC847,
3,R101 R108 R115,249k,,Resistor_SMD:R_0603_1608Metric,Device:R,
12,R102 R109 R116 R129 R131 R206 R402 R412 R423 R425 R514 R515,100k,,Resistor_SMD:R_0603_1608Metric,Device:R,
3,R103 R110 R117,41.2k,,Resistor_SMD:R_0603_1608Metric,Device:R,
22,R104 R107 R111 R118 R121 R124 R127 R204 R205 R209 R210 R302 R303 R304 R306 R427 R428 R431 R432 R518 R519 R520,10k,,Resistor_SMD:R_0603_1608Metric,Device:R,
2,R105 R112,30m,,Resistor_SMD:R_2512_6332Metric,Device:R,
1,R106,105k,,Resistor_SMD:R_0603_1608Metric,Device:R,
1,R113,110k,,Resistor_SMD:R_0603_1608Metric,Device:R,
1,R114,4.99k,,Resistor_SMD:R_0603_1608Metric,Device:R,
1,R119,100m,,Resistor_SMD:R_2512_6332Metric,Device:R,
1,R120,301k,,Resistor_SMD:R_0603_1608Metric,Device:R,
1,R122,4.7k,,Resistor_SMD:R_0603_1608Metric,Device:R,
1,R123,127k,,Resistor_SMD:R_0603_1608Metric,Device:R,
1,R125,33.2k,,Resistor_SMD:R_0603_1608Metric,Device:R,
1,R126,82.5k,,Resistor_SMD:R_0603_1608Metric,Device:R,
1,R128,316k,,Resistor_SMD:R_0603_1608Metric,Device:R,
1,R130,12.4k,,Resistor_SMD:R_0603_1608Metric,Device:R,
1,R201,1M,,Resistor_SMD:R_0603_1608Metric,Device:R,
3,R202 R421 R521,1k,,Resistor_SMD:R_0603_1608Metric,Device:R,
1,R203,100R,,Resistor_SMD:R_0805_2012Metric,Device:R,
2,R207 R208,2.2k,,Resistor_SMD:R_0603_1608Metric,Device:R,
3,R211 R212 R213,22R,,Resistor_SMD:R_0603_1608Metric,Device:R,
3,R214 R215 R216,33R,,Resistor_SMD:R_0603_1608Metric,Device:R,
2,R217 R218,330R,,Resistor_SMD:R_0603_1608Metric,Device:R,
1,R301,16k,,Resistor_SMD:R_0603_1608Metric,Device:R,
0,R305 R307,10k,,Resistor_SMD:R_0603_1608Metric,Device:R,DNP
4,R308 R309 R310 R311,750R 0.1%,,Resistor_SMD:R_0603_1608Metric,Device:R,
8,R312 R314 R316 R318 R403 R413 R512 R513,2.00k 0.1%,,Resistor_SMD:R_0603_1608Metric,Device:R,
4,R313 R315 R317 R319,1.00k 0.1%,,Resistor_SMD:R_0603_1608Metric,Device:R,
2,R401 R411,100R,,Resistor_SMD:R_0603_1608Metric,Device:R,
2,R404 R414,4.02k 0.1%,,Resistor_SMD:R_0603_1608Metric,Device:R,
2,R405 R415,576R 0.1%,,Resistor_SMD:R_0603_1608Metric,Device:R,
5,R406 R408 R416 R418 R501,47R,,Resistor_SMD:R_0603_1608Metric,Device:R,
4,R407 R409 R417 R419,2.2R 1W,,Resistor_SMD:R_2512_6332Metric,Device:R,
6,R410 R420 R507 R508 R509 R510,10R,,Resistor_SMD:R_0805_2012Metric,Device:R,
1,R422,220k,,Resistor_SMD:R_0603_1608Metric,Device:R,
1,R424,10.7k,,Resistor_SMD:R_0603_1608Metric,Device:R,
1,R426,16.9k,,Resistor_SMD:R_0603_1608Metric,Device:R,
2,R429 R430,47k,,Resistor_SMD:R_0603_1608Metric,Device:R,
1,R502,22k,,Resistor_SMD:R_0603_1608Metric,Device:R,
2,R503 R504,6.81k 0.1%,,Resistor_SMD:R_0805_2012Metric,Device:R,
2,R505 R506,2.21k,,Resistor_SMD:R_0603_1608Metric,Device:R,
1,R511,5.1R,,Resistor_SMD:R_0603_1608Metric,Device:R,
2,R516 R517,49.9R,,Resistor_SMD:R_0603_1608Metric,Device:R,
1,RV301,10k log dual,ALPS RK097 dual 10k log (A),Potentiometer_THT:Potentiometer_Alps_RK097_Dual_Horizontal,Device:R_Potentiometer_Dual,
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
